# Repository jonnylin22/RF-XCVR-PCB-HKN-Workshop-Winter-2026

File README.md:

# RF-XCVR-PCB-HKN-Workshop-Winter-2026

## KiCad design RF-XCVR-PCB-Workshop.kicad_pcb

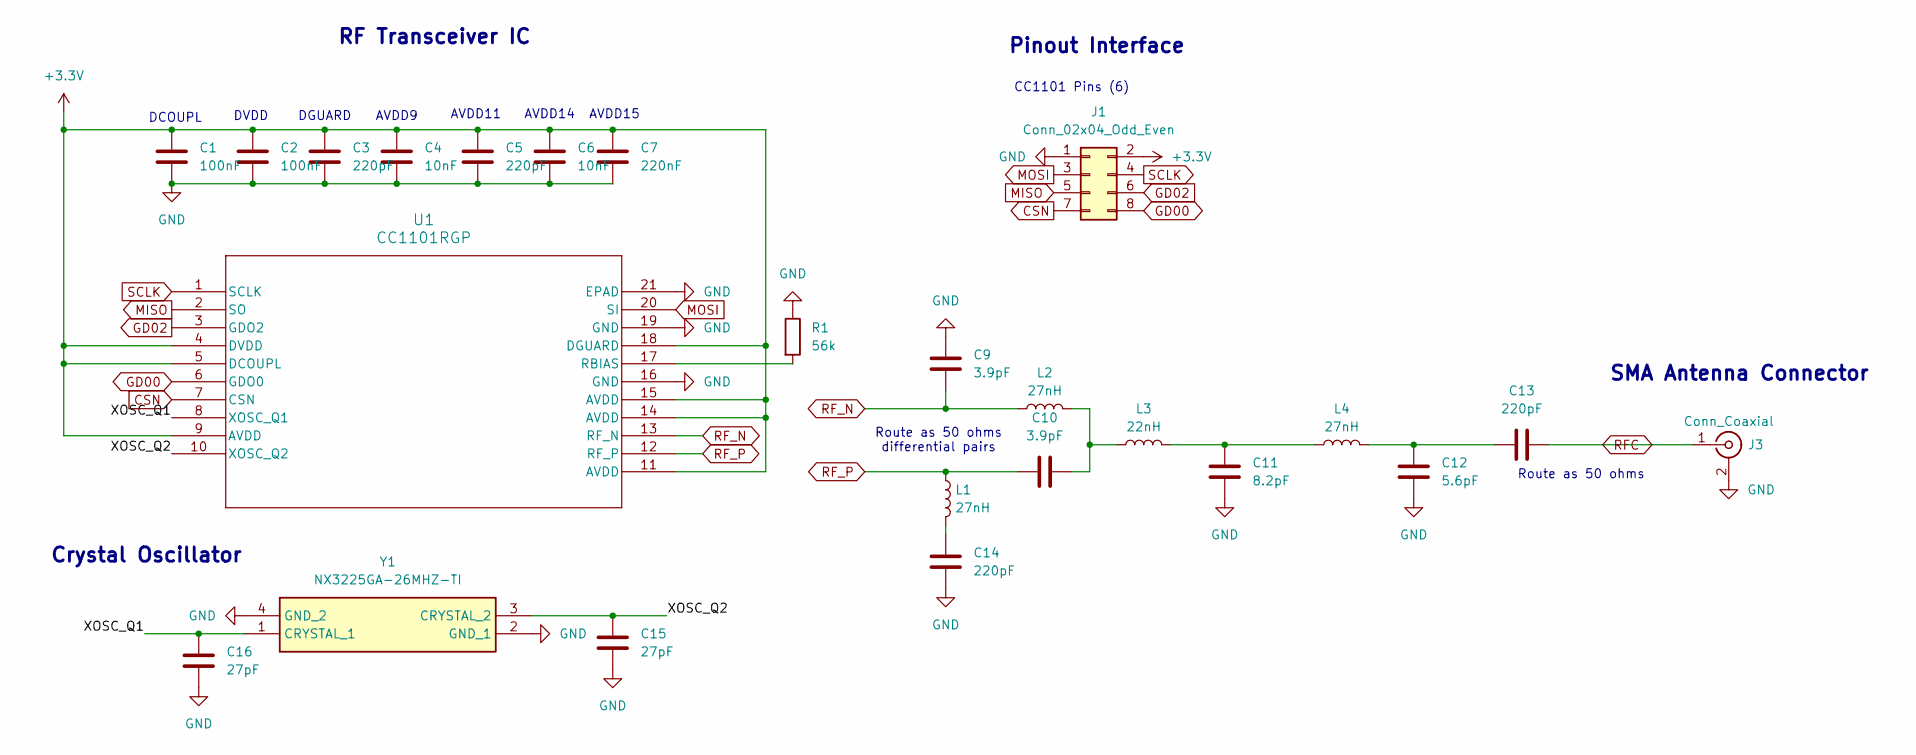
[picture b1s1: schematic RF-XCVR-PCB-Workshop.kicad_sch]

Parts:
C1, C2: 100nF; C_0402_1005Metric; Manufacturer_Part_Number GRM188R72A104KA35D; LCSC Part # C77058
C3, C5, C13, C14: 220pF; C_0402_1005Metric; Manufacturer_Part_Number GCM1885C1H221JA16D; LCSC Part # C126556
C4, C6: 10nF; C_0402_1005Metric; Manufacturer_Part_Number GRM188R72A103KA01D; LCSC Part # C162275
C7: 220nF; C_0402_1005Metric; Manufacturer_Part_Number GRM188R71E224KA88D; LCSC Part # C77051
C9, C10: 3.9pF; C_0402_1005Metric; Manufacturer_Part_Number Kyocera AVX 600S3R9BT250XT; LCSC Part # C3849659
C11: 8.2pF; C_0402_1005Metric; Manufacturer_Part_Number GQM1875C2E8R2CB12D; LCSC Part # C3874850
C12: 5.6pF; C_0402_1005Metric; Manufacturer_Part_Number GQM1875C2E5R6BB12D; LCSC Part # C2297617
C15, C16: 27pF; C_0402_1005Metric; Manufacturer_Part_Number GCM1885C2A270JA16D; LCSC Part # C909846
J1: Conn_02x04_Odd_Even; PinHeader_2x04_P2.54mm_Vertical
J3: Conn_Coaxial; SMA_Molex_73251-1153_EdgeMount_Horizontal; Manufacturer_Part_Number 132134; LCSC Part # C3174425
L1, L2, L4: 27nH; L_0402_1005Metric; Manufacturer_Part_Number LQG15HS4N7S02D; LCSC Part # C86065
L3: 22nH; L_0402_1005Metric; Manufacturer_Part_Number LQG15HS22NJ02D; LCSC Part # C12670
R1: 56k; R_0402_1005Metric
U1: CC1101RGP; RGP20_2P4X2P4
Y1: NX3225GA-26MHZ-TI; NX3225GA26MHZTI; Mouser Part Number 344-NX3225GA26MHZTI

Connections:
+3.3V: C1.1, C2.1, C3.1, C4.1, C5.1, C6.1, C7.1, J1.2, U1.4 (DVDD), U1.5 (DCOUPL), U1.9 (AVDD), U1.11 (AVDD), U1.14 (AVDD), U1.15 (AVDD), U1.18 (DGUARD)
/XOSC_Q1: C16.2, U1.8 (XOSC_Q1), Y1.1 (CRYSTAL_1)
/XOSC_Q2: C15.2, U1.10 (XOSC_Q2), Y1.3 (CRYSTAL_2)
CSN: J1.7, U1.7 (CSN)
GD00: J1.8, U1.6 (GDO0)
GD02: J1.6, U1.3 (GDO2)
GND: C1.2, C2.2, C3.2, C4.2, C5.2, C6.2, C7.2, C9.1, C11.1, C12.1, C14.1, C15.1, C16.1, J1.1, J3.2 (Ext), R1.1, U1.16 (GND), U1.19 (GND), U1.21 (EPAD), U1.V, Y1.2 (GND_1), Y1.4 (GND_2)
MISO: J1.5, U1.2 (SO)
MOSI: J1.3, U1.20 (SI)
unnamed: C10.2, L2.2, L3.1
unnamed: C11.2, L3.2, L4.1
unnamed: C12.2, C13.2, L4.2
unnamed: C14.2, L1.2
unnamed: R1.2, U1.17 (RBIAS)
RFC: C13.1, J3.1 (In)
RF_N: C9.2, L2.1, U1.13 (RF_N)
RF_P: C10.1, L1.1, U1.12 (RF_P)
SCLK: J1.4, U1.1 (SCLK)

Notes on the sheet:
SMA Antenna Connector
Crystal Oscillator
AVDD14
DCOUPL
RF Transceiver IC
Route as 50 ohms differential pairs
Pinout Interface
DVDD
CC1101 Pins (6)
AVDD11
AVDD9
AVDD15
Route as 50 ohms
DGUARD

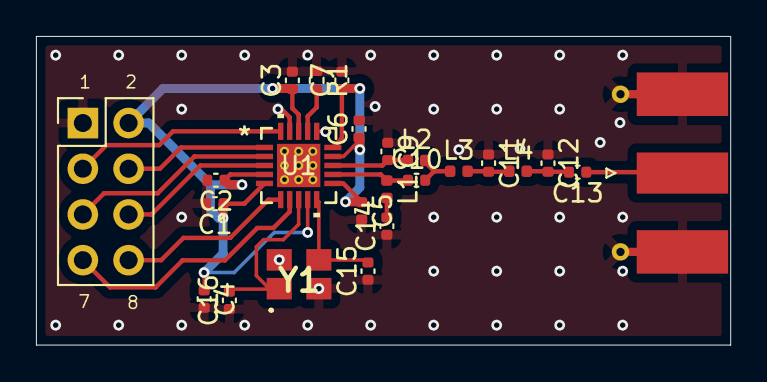
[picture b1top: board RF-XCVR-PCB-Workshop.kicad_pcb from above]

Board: 2 copper layers, 38.6 x 17.1 mm, 24 parts (0 on the bottom side), 18 nets.

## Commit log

2026-02-07 added gitignore
2026-02-11 bare CC1101 XCVR laid out
2026-02-12 updates?
